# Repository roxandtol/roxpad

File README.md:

# roxpad HE
3k keypad based on the [minipad](https://github.com/minipadKB), a Wooting style keypad, it uses the same firmware

I've designed the keypad using [KiCad](https://www.kicad.org/) for the PCB, and [OnShape](https://www.onshape.com/en/) for the case.

---
# Making it
**⚠️⚠️⚠️ This keypad is still a WIP ⚠️⚠️⚠️**

You will need:
1) The components:
    |Component|Quantity|
    |---|---|
    |[Raspberry Pi Pico](https://es.aliexpress.com/item/1005003796653297.html)|1|
    |[Lekker Switches](https://next.wooting.io/product/lekker-switch-linear60-12-pack) (you should be able to just use some modded switches aswell|3|
    |[SLSS49E Hall Effect sensor](https://www.lcsc.com/product-detail/Hall-Sensor_Slkor-SLKORMICRO-Elec-SLSS49E-3_C2904393.html)|3|
    
1) The PCB design in [The releases tab](https://github.com/roxandtol/roxpad/releases/latest)
1) The [3d design](https://www.printables.com/model/421393-roxpad-v2)
1) A soldering iron
1) 4 m3*22 screws with their nuts
1) Hot glue (for the feet)

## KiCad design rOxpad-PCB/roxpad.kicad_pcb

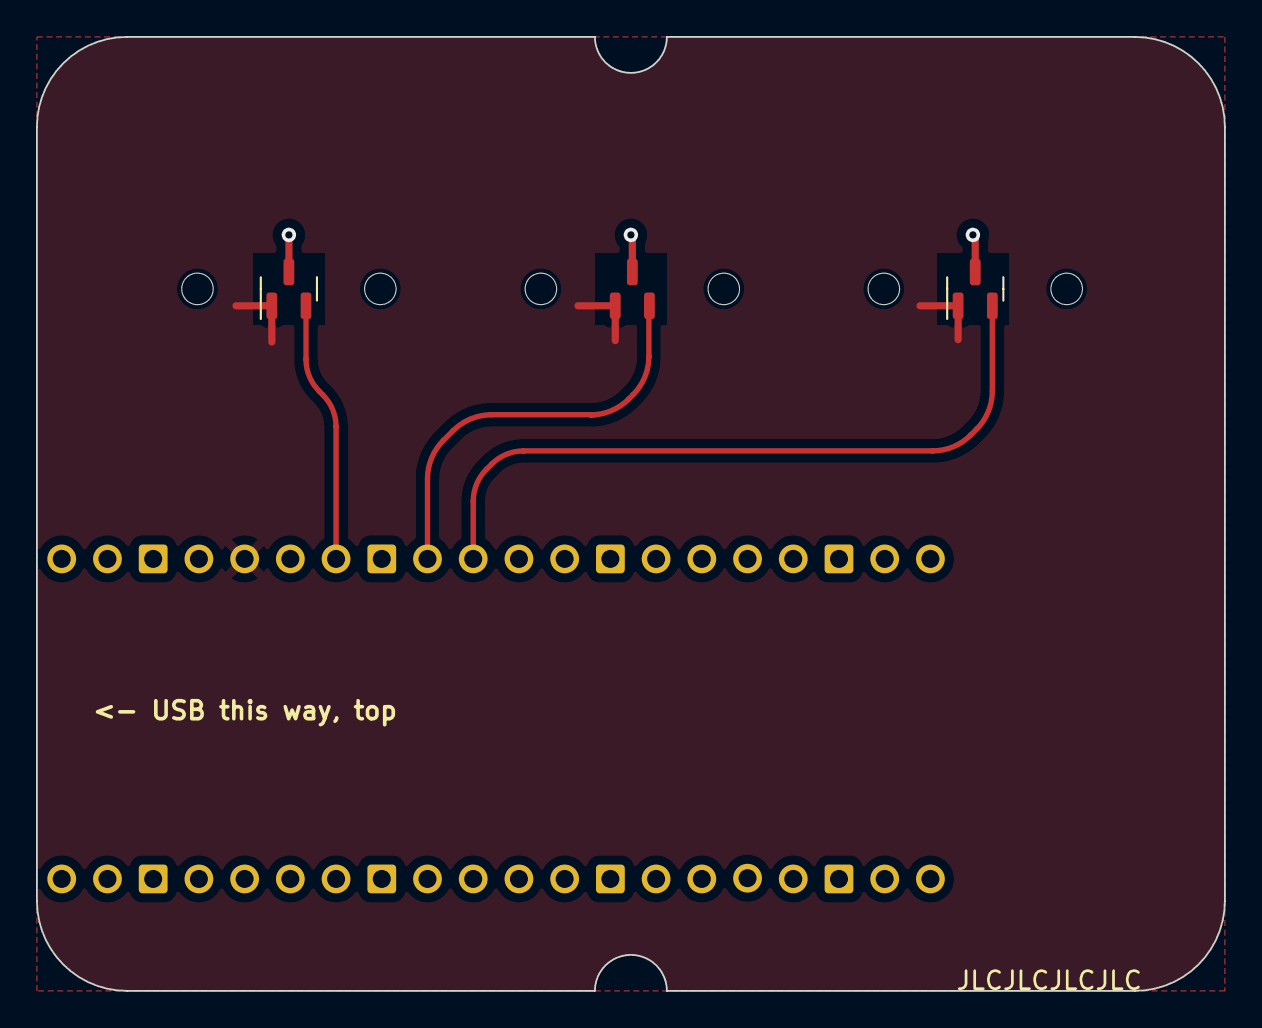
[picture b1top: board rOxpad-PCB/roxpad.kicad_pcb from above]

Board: 2 copper layers, 66.0 x 53.0 mm, 4 parts (0 on the bottom side), 5 nets.

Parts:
H1, H2, H3: SS49E; SOT-23
Pi_Pico1: SC0915; MODULE_SC0915

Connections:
unnamed: H1.3 (GND), H2.3 (GND), H3.3 (GND), Pi_Pico1.33 (AGND)
unnamed: H1.2 (OUT), Pi_Pico1.34 (GP28)
unnamed: H1.1 (VDD), H2.1 (VDD), H3.1 (VDD), Pi_Pico1.36 (3V3_OUT)
unnamed: H2.2 (OUT), Pi_Pico1.32 (GP27)
unnamed: H3.2 (OUT), Pi_Pico1.31 (GP26)

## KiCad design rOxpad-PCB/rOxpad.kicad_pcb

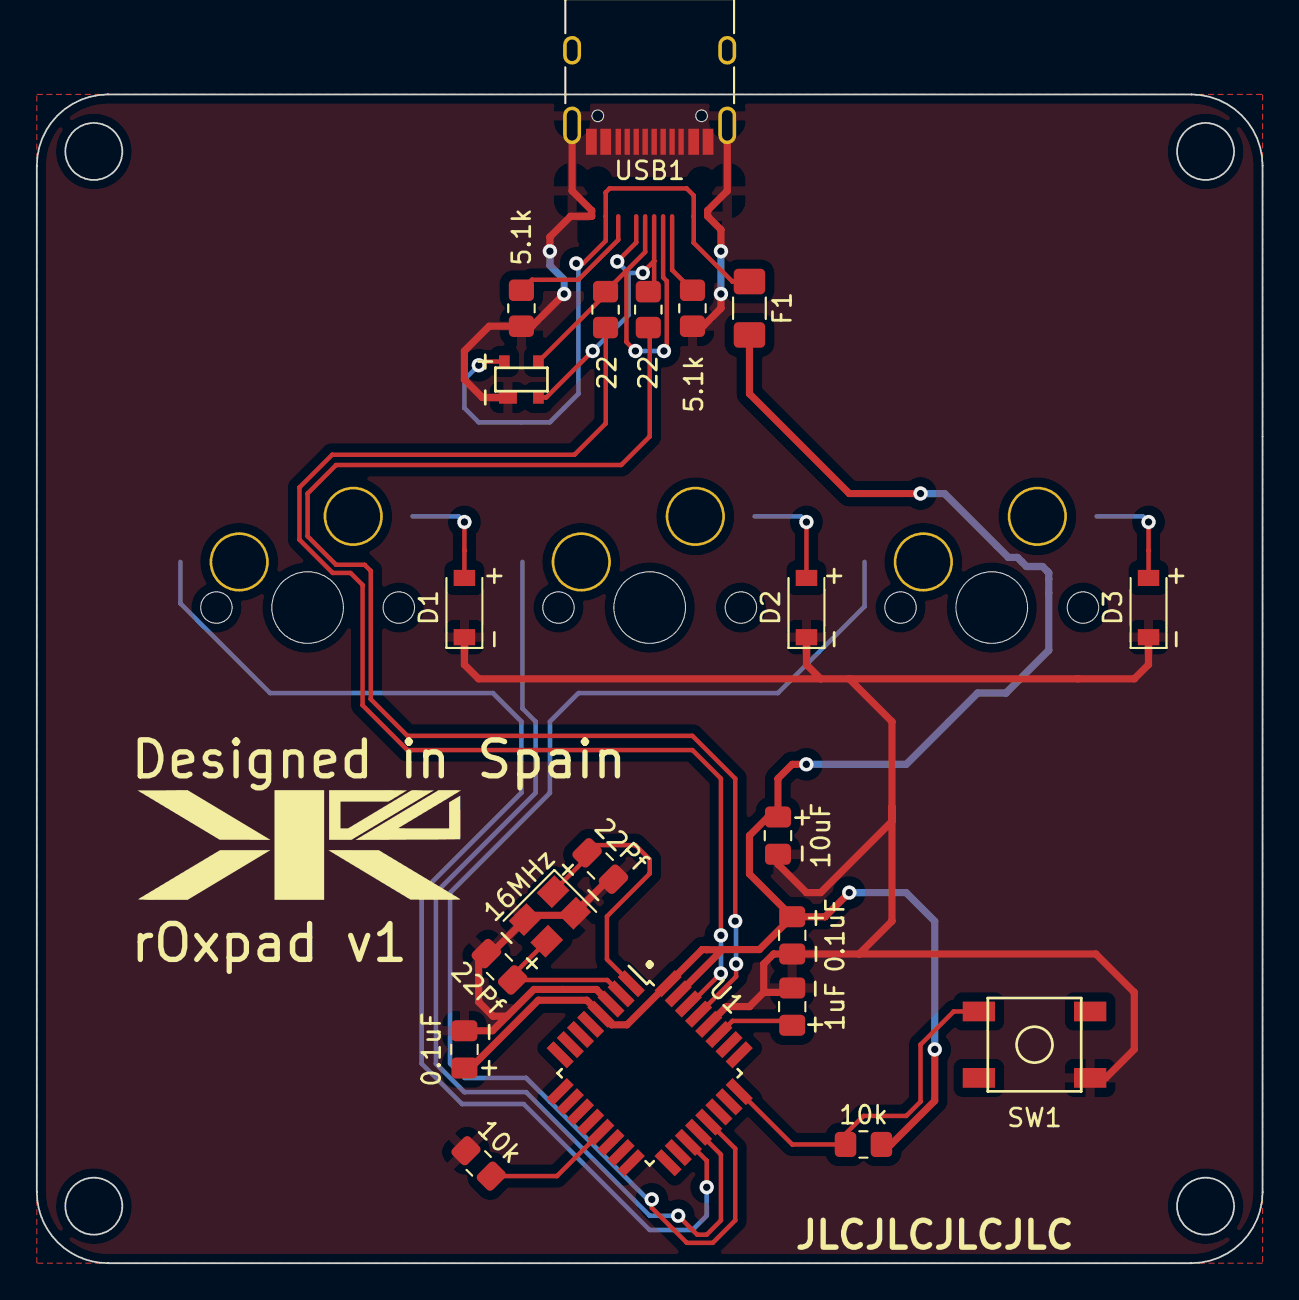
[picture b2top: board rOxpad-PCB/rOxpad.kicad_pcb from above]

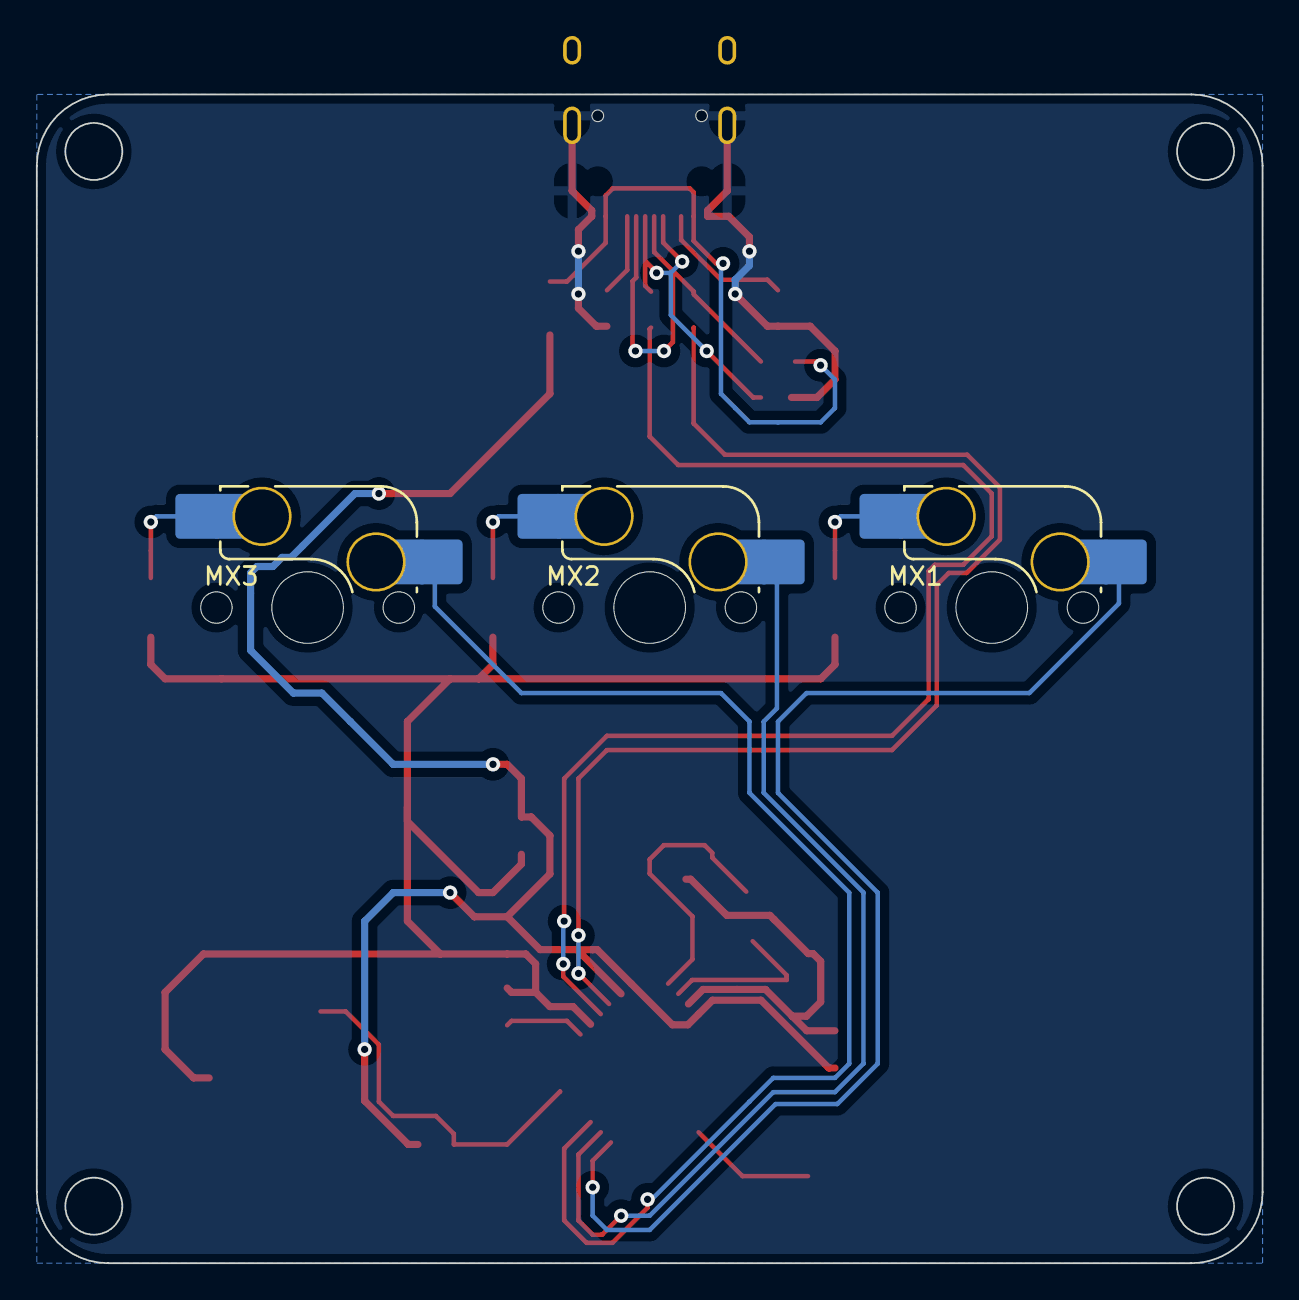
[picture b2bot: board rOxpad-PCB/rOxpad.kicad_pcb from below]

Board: 2 copper layers, 68.3 x 65.1 mm, 24 parts (3 on the bottom side), 12 nets.

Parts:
C1: 1uF; C_0805_2012Metric_Pad1.18x1.45mm_HandSolder
C2, C3: 22Pf; C_0805_2012Metric_Pad1.18x1.45mm_HandSolder
C4, C5: 0.1uF; C_0805_2012Metric_Pad1.18x1.45mm_HandSolder
C7: 10uF; C_0805_2012Metric_Pad1.18x1.45mm_HandSolder
D1, D2, D3: D_Small; D_SOD-123
F1: Polyfuse_Small; Fuse_1206_3216Metric_Pad1.42x1.75mm_HandSolder
MX1, MX2, MX3: MX-NoLED; SW_MX_HS_1u
R1, R2: 22; R_0805_2012Metric_Pad1.20x1.40mm_HandSolder
R3, R4: 10k; R_0805_2012Metric_Pad1.20x1.40mm_HandSolder
R5, R6: 5.1k; R_0805_2012Metric_Pad1.20x1.40mm_HandSolder
SW1: SW_Push; SKQG-1155865
U1: ATmega32U2-A; TQFP-32_7x7mm_P0.8mm
U2: PRTR5V0U2X; SOT143B
USB1: HRO-TYPE-C-31-M-12; USB_C_Receptacle_HRO_TYPE-C-31-M-12
Y1: 16MHz; Crystal_SMD_3225-4Pin_3.2x2.5mm

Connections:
+5V: C4.1, C5.1, C7.1, F1.2, R3.1, U1.31 (UVCC)
D+: R2.1, U2.2 (IO1)
D-: R1.1, U2.3 (IO2)
GND: C1.2, C2.1, C3.1, C4.2, C5.2, C7.2, D1.1 (K), D2.1 (K), D3.1 (K), R4.2, R5.2, R6.2, SW1.1, U1.28 (UGND), U2.1 (GND), Y1.2, Y1.4
unnamed: D1.2 (A), MX1.2 (ROW)
unnamed: D2.2 (A), MX2.2 (ROW)
unnamed: D3.2 (A), MX3.2 (ROW)
unnamed: R3.2, SW1.2
unnamed: R4.1, U1.13 (~HWB/PD7)
VCC: F1.1, U2.4 (VCC)
XTAL1: C2.2, Y1.1
XTAL2: C3.2, Y1.3

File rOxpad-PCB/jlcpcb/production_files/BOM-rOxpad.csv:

Comment,Designator,Footprint,LCSC
16MHz,Y1,Crystal_SMD_3225-4Pin_3.2x2.5mm,C13738
Polyfuse,F1,Fuse_1206_3216Metric_Pad1.42x1.75mm_HandSolder,C151162
10uF,C7,C_0805_2012Metric_Pad1.18x1.45mm_HandSolder,C15850
HRO-TYPE-C-31-M-12,USB1,HRO-TYPE-C-31-M-12-HandSoldering,C165948
10kΩ,R3;R4,R_0805_2012Metric_Pad1.20x1.40mm_HandSolder,C17414
22Ω,R1;R2,R_0805_2012Metric_Pad1.20x1.40mm_HandSolder,C17561
22Pf,C2;C3,C_0805_2012Metric_Pad1.18x1.45mm_HandSolder,C1804
5.1kΩ,R5;R6,R_0805_2012Metric_Pad1.20x1.40mm_HandSolder,C27834
MX-NoLED,MX1;MX2;MX3,SW_MX_HS_1u,C2803348
PRTR5V0U2X,U2,SOT143B,C2827688
1uF,C1,C_0805_2012Metric_Pad1.18x1.45mm_HandSolder,C28323
0.1uF,C4;C5,C_0805_2012Metric_Pad1.18x1.45mm_HandSolder,C49678
ATmega16U2-A,U1,TQFP-32_7x7mm_P0.8mm,C59019
D_Small,D1;D2;D3,D_SOD-123,C81598

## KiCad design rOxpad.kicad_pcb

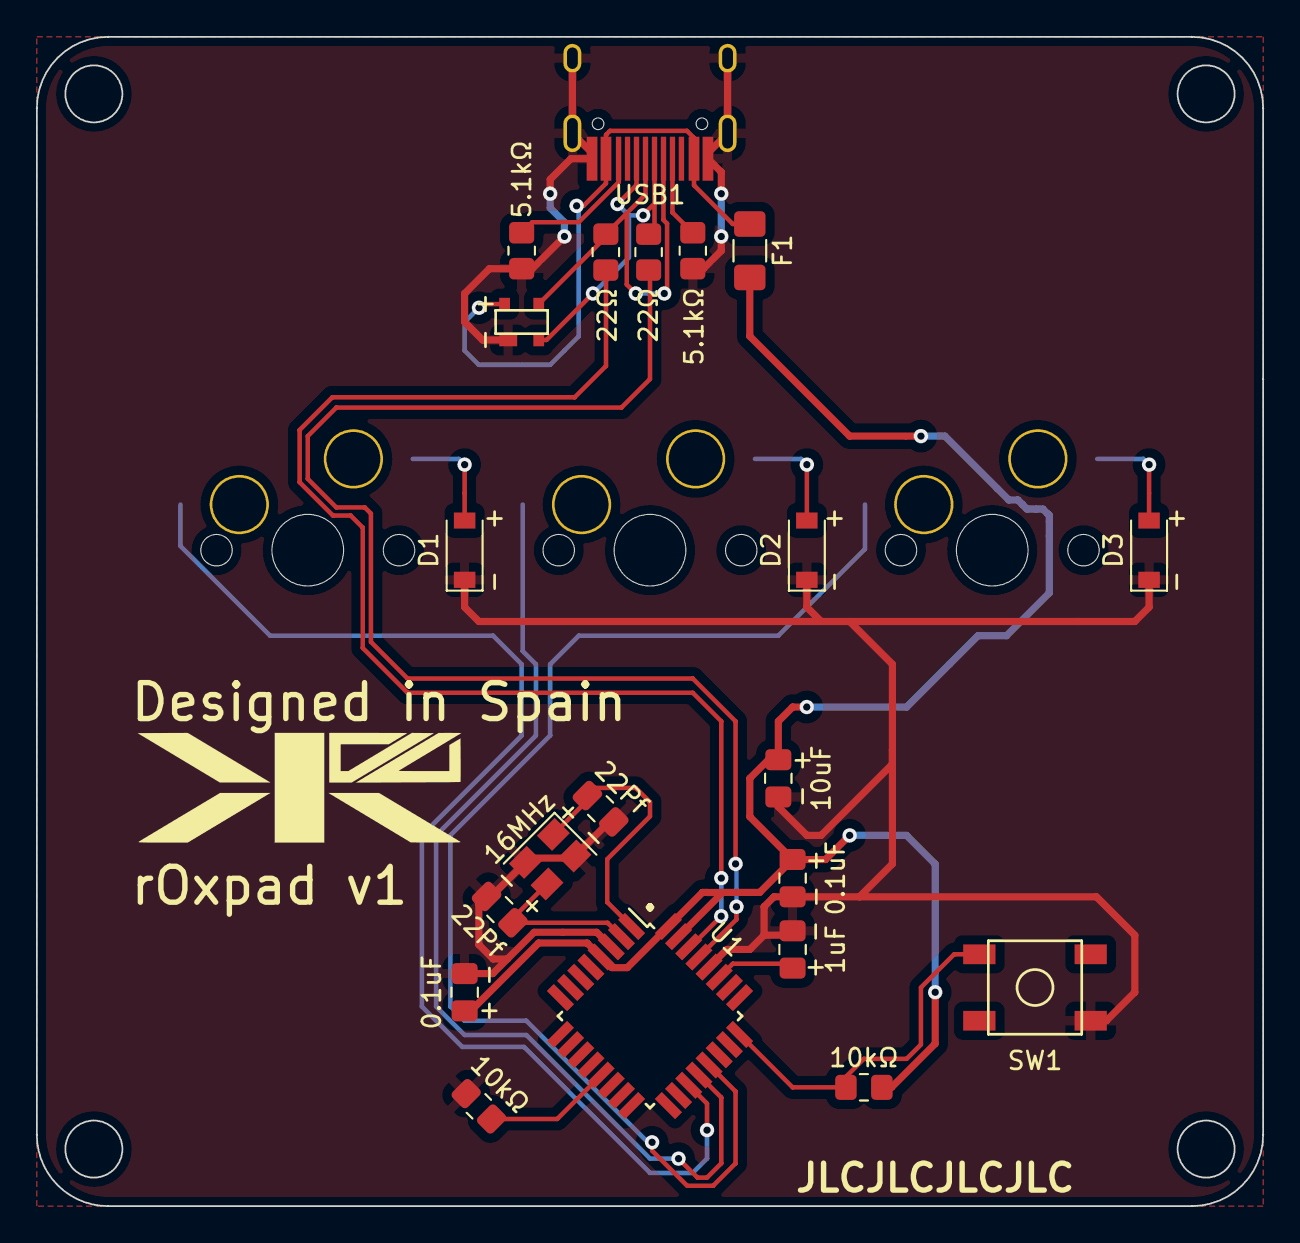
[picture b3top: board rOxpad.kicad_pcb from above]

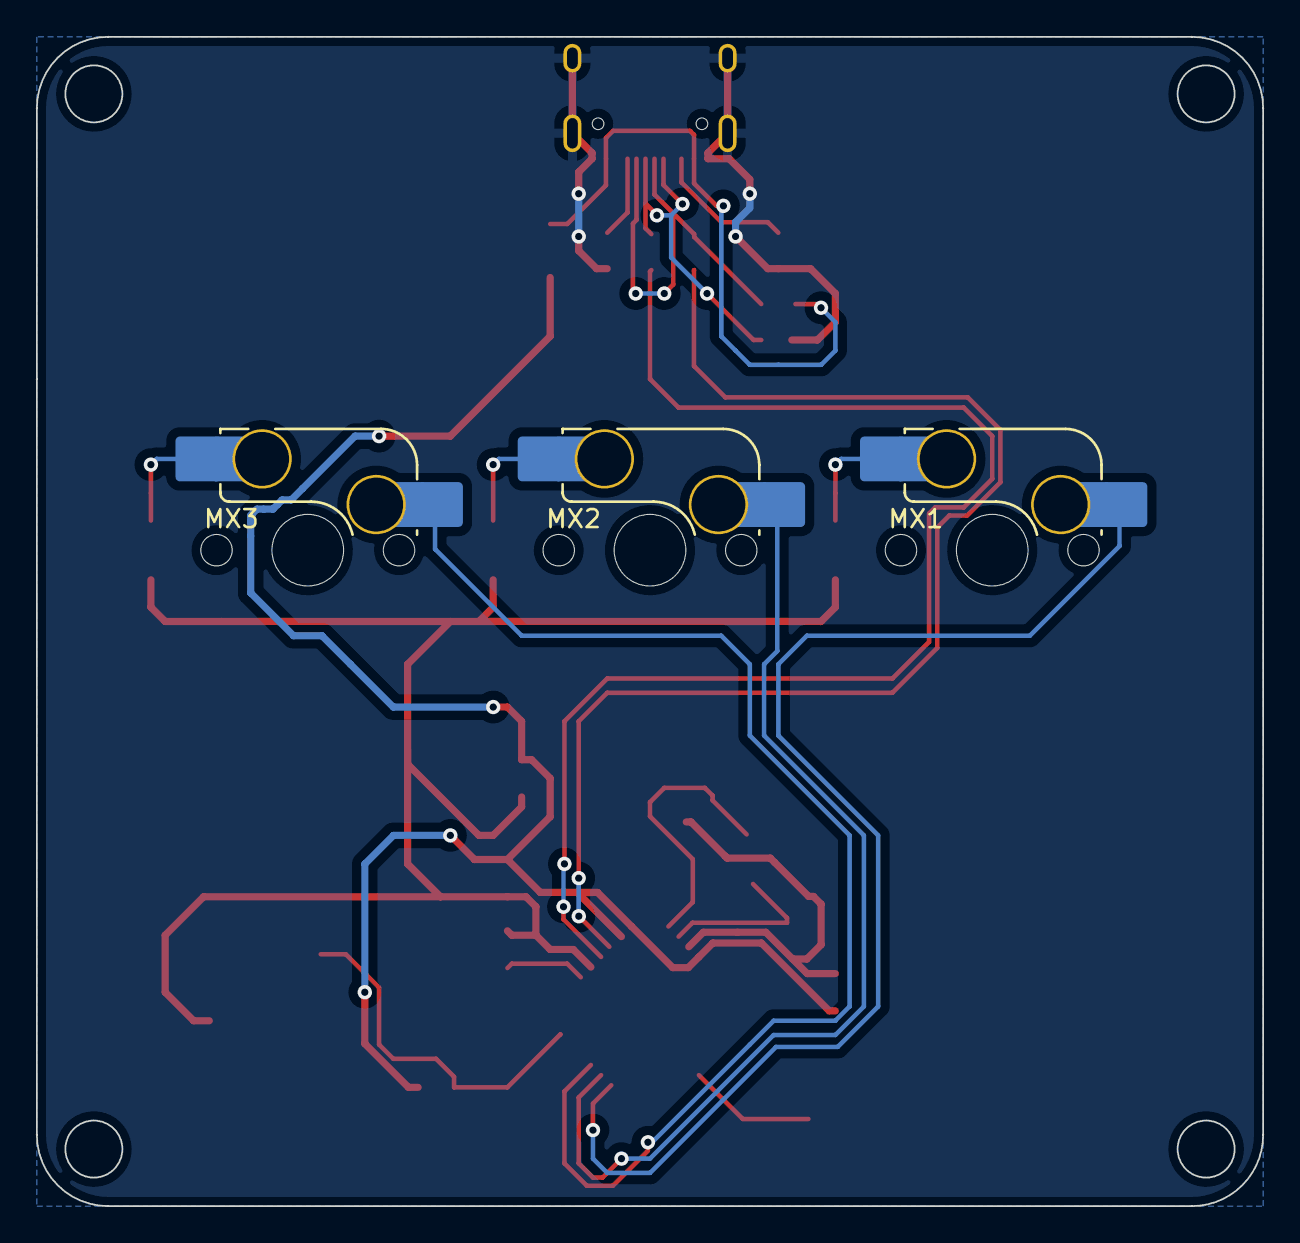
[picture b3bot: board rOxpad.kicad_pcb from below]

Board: 2 copper layers, 68.3 x 65.1 mm, 24 parts (3 on the bottom side), 20 nets.

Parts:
C1: 1uF; C_0805_2012Metric_Pad1.18x1.45mm_HandSolder
C2, C3: 22Pf; C_0805_2012Metric_Pad1.18x1.45mm_HandSolder
C4, C5: 0.1uF; C_0805_2012Metric_Pad1.18x1.45mm_HandSolder
C7: 10uF; C_0805_2012Metric_Pad1.18x1.45mm_HandSolder
D1, D2, D3: D_Small; D_SOD-123
F1: Polyfuse; Fuse_1206_3216Metric_Pad1.42x1.75mm_HandSolder
MX1, MX2, MX3: MX-NoLED; SW_MX_HS_1u
R1, R2: 22Ω; R_0805_2012Metric_Pad1.20x1.40mm_HandSolder
R3, R4: 10kΩ; R_0805_2012Metric_Pad1.20x1.40mm_HandSolder
R5, R6: 5.1kΩ; R_0805_2012Metric_Pad1.20x1.40mm_HandSolder
SW1: SW_Push; SKQG-1155865
U1: ATmega16U2-A; TQFP-32_7x7mm_P0.8mm
U2: PRTR5V0U2X; SOT143B
USB1: HRO-TYPE-C-31-M-12; HRO-TYPE-C-31-M-12-HandSoldering
Y1: 16MHz; Crystal_SMD_3225-4Pin_3.2x2.5mm

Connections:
+5V: C4.1, C5.1, C7.1, F1.2, R3.1, U1.4 (VCC), U1.31 (UVCC), U1.32 (AVCC)
D+: R2.1, U2.2 (IO1), USB1.6 (DP1), USB1.8 (DP2)
D-: R1.1, U2.3 (IO2), USB1.5 (DN2), USB1.7 (DN1)
GND: C1.2, C2.1, C3.1, C4.2, C5.2, C7.2, D1.1 (K), D2.1 (K), D3.1 (K), R4.2, R5.2, R6.2, SW1.1, U1.3 (GND), U1.28 (UGND), U2.1 (GND), USB1.1 (GND), USB1.12 (GND), USB1.13 (SHIELD), Y1.2, Y1.4
KEY-0: MX1.1 (COL), U1.19 (PB5)
KEY-1: MX2.1 (COL), U1.20 (PB6)
KEY-2: MX3.1 (COL), U1.21 (PB7)
unnamed: C1.1, U1.27 (UCAP)
unnamed: D1.2 (A), MX1.2 (ROW)
unnamed: D2.2 (A), MX2.2 (ROW)
unnamed: D3.2 (A), MX3.2 (ROW)
unnamed: R1.2, U1.30 (D-)
unnamed: R2.2, U1.29 (D+)
unnamed: R3.2, SW1.2, U1.24 (PC1/~RESET)
unnamed: R4.1, U1.13 (~HWB/PD7)
unnamed: R5.1, USB1.4 (CC1)
unnamed: R6.1, USB1.10 (CC2)
VCC: F1.1, U2.4 (VCC), USB1.2 (VBUS), USB1.11 (VBUS)
XTAL1: C2.2, U1.1 (XTAL1), Y1.1
XTAL2: C3.2, U1.2 (PC0/XTAL2), Y1.3

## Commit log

2022-12-07 Create the project
    in Kicad
2022-12-07 Add submodules
2022-12-07 added some libraries
2022-12-07 design most of the base keypad schem
2022-12-07 Applied footprints!
2022-12-08 I think the pcb is done wohoo
2022-12-08 might've forgot to save whoops
2022-12-08 started redesigning the schematic
    didn't like the result lol
2022-12-08 add another submodule, and continue with schem v2
2022-12-08 I think it's finished wohoo
2022-12-08 create gitignore and change hole size
2022-12-08 Made some changes so it's doesn't explode
2022-12-08 it was a square oops
2022-12-09 add case DXF files
2022-12-09 Fix sizing
2022-12-09 change a bit the gitignore
2022-12-09 add marbstlib
2022-12-09 Changed switch footprint (still same connections)
2022-12-09 Main board wiring finished (i hope)
2022-12-09 Finished all component markings
2022-12-09 add random folder to gitignore
2022-12-09 finishing touches
2022-12-09 try new plugin
2022-12-09 change some stuff
2022-12-09 moved everything to a subfolder
2022-12-09 forgot to update gitmodules whoops
2022-12-10 remove submodules
    going to readd them
2022-12-10 readd submodules
2022-12-11 change diode array to ESD protection circuit in readme
2022-12-11 create firmware
2022-12-11 make the keymap
2022-12-11 try to fix some things (couldn't fix them)
2022-12-14 change MCU to atmega32u2
    a lot cheaper
2023-03-10 start fresh
2023-03-10 make pcb
2023-03-10 fix pinout (thanks Bexin!)
2023-03-12 update 3d print file
2023-03-13 change ' hall sensor`to proper sensor name
2023-03-13 online BOM
2023-03-13 changed designations
2023-03-13 update gitignore
2023-04-17 change GND from seriees to paralel, and add support
    Sucks because I had already ordered the board, and recieved it, and soldered the pi pico. AAAAAAAAAAAAAAAAAAAAAAAAAAAAAAAAAAAAAAAAAAAAAAAAAAAAAAAAA
2023-04-23 fix keypad again and make it swag
2024-03-20 changed gnd to agnd
    I think this fixes it, won't check
